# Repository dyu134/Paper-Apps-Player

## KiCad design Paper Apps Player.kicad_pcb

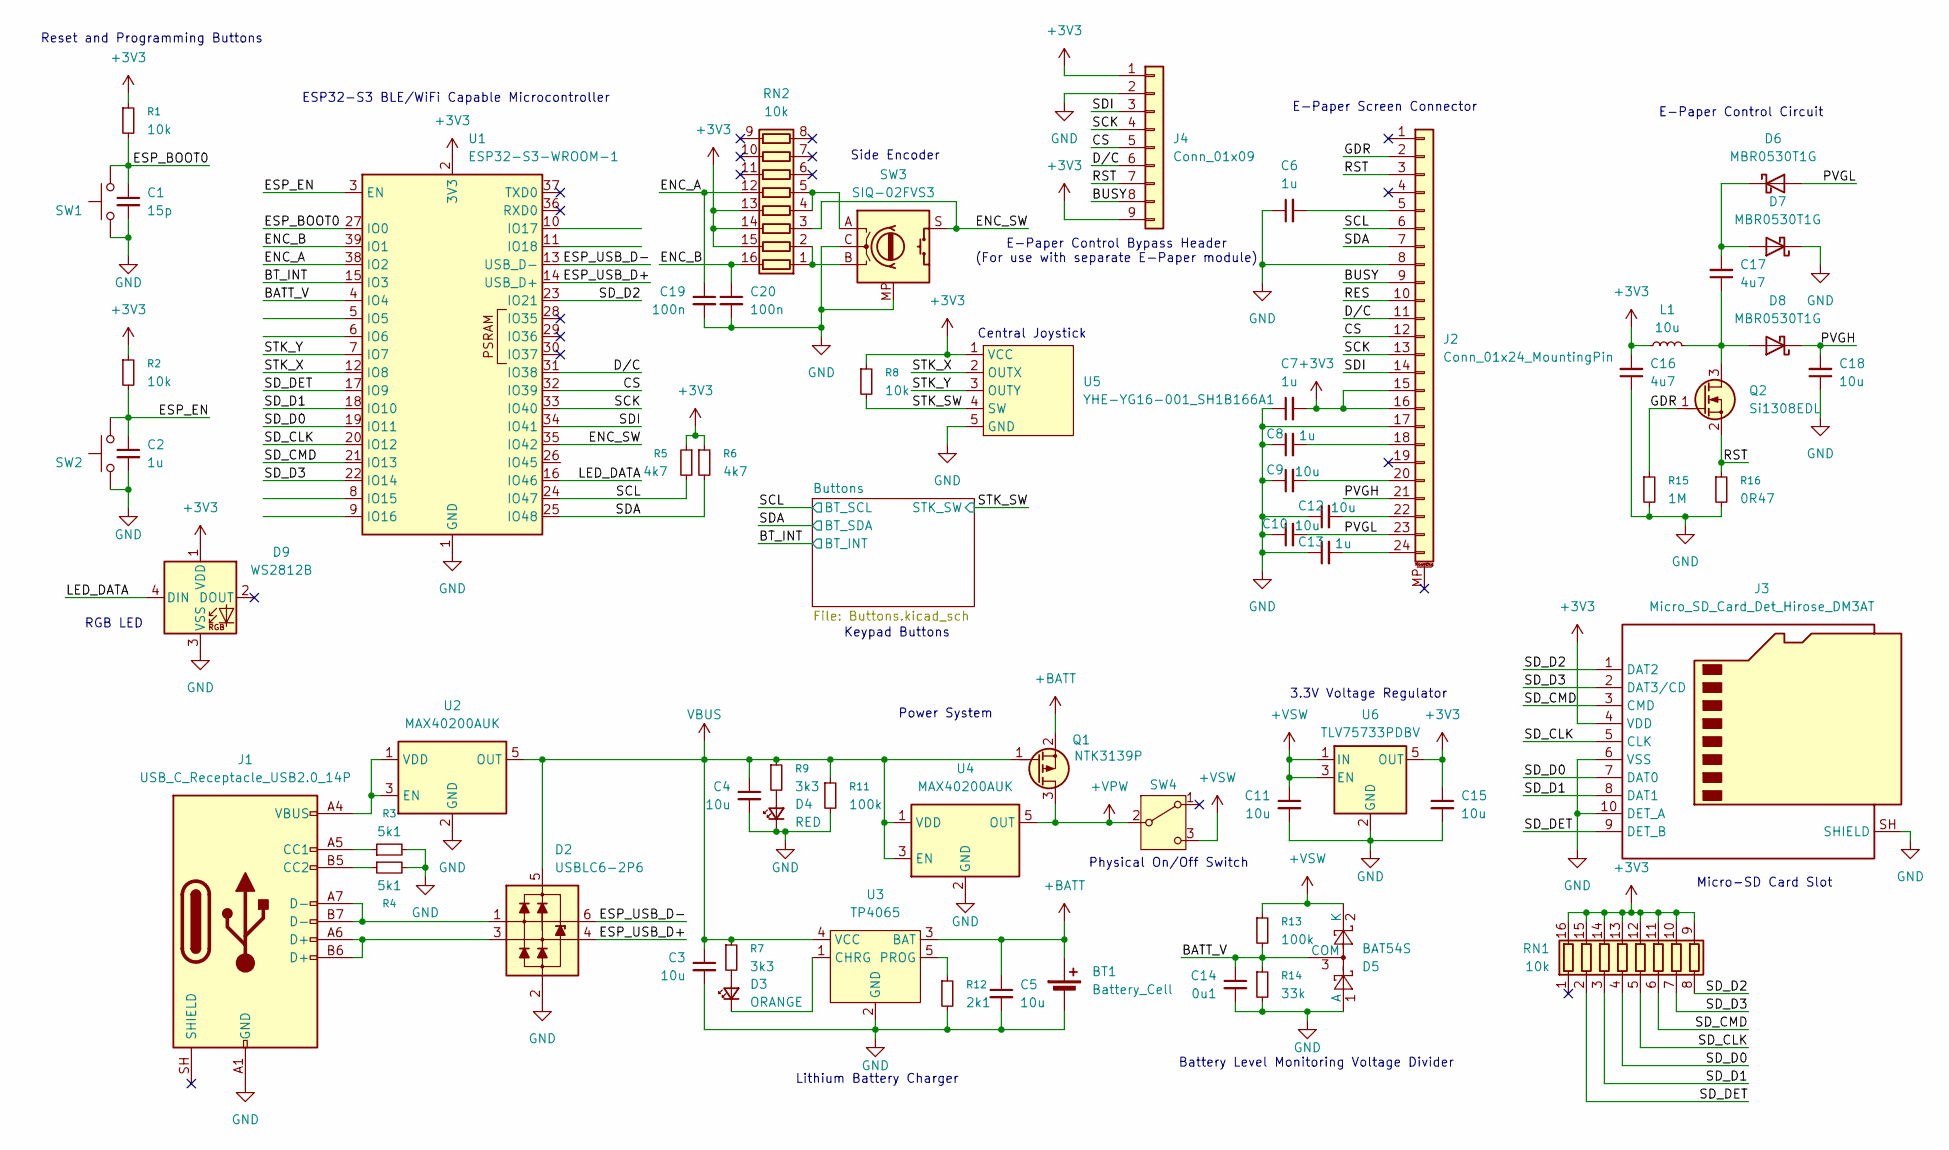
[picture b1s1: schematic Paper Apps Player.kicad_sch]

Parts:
BT1: Battery_Cell; Molex_PicoBlade_53048-0210_1x02_P1.25mm_Horizontal
C1: 15p; C_0603_1608Metric
C2, C6, C7, C8, C13: 1u; C_0603_1608Metric
C3, C4, C5, C9, C10, C11, C12, C15, C18: 10u; C_0603_1608Metric
C14: 0u1; C_0603_1608Metric
C16, C17: 4u7; C_0603_1608Metric
C19, C20: 100n; C_0603_1608Metric
D2: USBLC6-2P6; SOT-666
D3: ORANGE; LED_0603_1608Metric
D4: RED; LED_0603_1608Metric
D5: BAT54S; SOT-23
D6, D7, D8: MBR0530T1G; D_SOD-123
D9: WS2812B; LED_WS2812B_PLCC4_5.0x5.0mm_P3.2mm
J1: USB_C_Receptacle_USB2.0_14P; USB_C_Receptacle_HCTL_HC-TYPE-C-16P-01A
J2: Conn_01x24_MountingPin; Hirose_FH12-24S-0.5SH_1x24-1MP_P0.50mm_Horizontal
J3: Micro_SD_Card_Det_Hirose_DM3AT; microSD_HC_Hirose_DM3AT-SF-PEJM5
J4: Conn_01x09; PinHeader_1x09_P2.54mm_Vertical
L1: 10u; L_0603_1608Metric
Q1: NTK3139P; SOT-723
Q2: Si1308EDL; SOT-323_SC-70
R1, R2: 10k; R_0402_1005Metric
R3, R4: 5k1; R_0603_1608Metric
R5, R6: 4k7; R_0603_1608Metric
R7, R9: 3k3; R_0603_1608Metric
R8: 10k; R_0603_1608Metric
R11, R13: 100k; R_0603_1608Metric
R12: 2k1; R_0603_1608Metric
R14: 33k; R_0603_1608Metric
R15: 1M; R_0603_1608Metric
R16: 0R47; R_0603_1608Metric
RN1, RN2: 10k; R_Array_Convex_8x0602
SW1, SW2: SKRPACE010; SW_Push_1P1T_NO_Vertical_Wuerth_434133025816
SW3: SIQ-02FVS3
SW4: JS102011SAQN; SW_SPDT_CK_JS102011SAQN
U1: ESP32-S3-WROOM-1
U2, U4: MAX40200AUK; SOT-23-5
U3: TP4065; SOT-23-5_HandSoldering
U5: YHE-YG16-001_SH1B166A1
U6: TLV75733PDBV; SOT-23-5

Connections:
+3V3: C7.2, C15.1, C16.2, D9.1 (VDD), J2.15, J2.16, J3.4 (VDD), J4.1, J4.9, L1.1, R1.1, R2.1, R5.1, R6.1, R8.1, RN1.9 (R8.2), RN1.10 (R7.2), RN1.11 (R6.2), RN1.12 (R5.2), RN1.13 (R4.2), RN1.14 (R3.2), RN1.15 (R2.2), RN1.16 (R1.2), RN2.13 (R4.2), RN2.14 (R3.2), RN2.15 (R2.2), U1.2 (3V3), U5.1 (VCC), U6.5 (OUT); also elsewhere on the board
+BATT: BT1.1 (+), C5.1, Q1.2 (S), U3.3 (BAT)
+VPW: Q1.3 (D), SW4.2 (B), U4.5 (OUT)
+VSW: C11.1, D5.2 (K), R13.1, SW4.3 (C), U6.1 (IN), U6.3 (EN)
/BATT_V: C14.1, D5.3 (COM), R13.2, R14.1, U1.4 (IO4)
/BT_INT: U1.15 (IO3); also elsewhere on the board
/BUSY: J2.9, J4.8
/CS: J2.12, J4.5, U1.32 (IO39)
/D/C: J2.11, J4.6, U1.31 (IO38)
/ENC_A: C19.1, RN2.12 (R5.2), U1.38 (IO2)
/ENC_B: C20.1, RN2.16 (R1.2), U1.39 (IO1)
/ENC_SW: RN2.3 (R3.1), SW3.S, U1.35 (IO42)
/ESP_BOOT0: C1.1, R1.2, SW1.2, U1.27 (IO0)
/ESP_EN: C2.1, R2.2, SW2.2, U1.3 (EN)
/ESP_USB_D+: D2.4 (L2), U1.14 (USB_D+)
/ESP_USB_D-: D2.6 (L1), U1.13 (USB_D-)
/GDR: J2.2, Q2.1 (G), R15.1
/LED_DATA: D9.4 (DIN), U1.16 (IO46)
/PVGH: C18.2, D8.1 (K), J2.21
/PVGL: C10.2, D6.2 (A), J2.23
/RES: J2.10
/RST: J2.3, J4.7, Q2.2 (S), R16.1
/SCK: J2.13, J4.4, U1.33 (IO40)
/SCL: J2.6, R5.2, U1.24 (IO47); also elsewhere on the board
/SDA: J2.7, R6.2, U1.25 (IO48); also elsewhere on the board
/SDI: J2.14, J4.3, U1.34 (IO41)
/SD_CLK: J3.5 (CLK), RN1.5 (R5.1), U1.20 (IO12)
/SD_CMD: J3.3 (CMD), RN1.6 (R6.1), U1.21 (IO13)
/SD_D0: J3.7 (DAT0), RN1.4 (R4.1), U1.19 (IO11)
/SD_D1: J3.8 (DAT1), RN1.3 (R3.1), U1.18 (IO10)
/SD_D2: J3.1 (DAT2), RN1.8 (R8.1), U1.23 (IO21)
/SD_D3: J3.2 (DAT3/CD), RN1.7 (R7.1), U1.22 (IO14)
/SD_DET: J3.9 (DET_B), RN1.2 (R2.1), U1.17 (IO9)
/STK_SW: R8.2, U5.4 (SW); also elsewhere on the board
/STK_X: U1.12 (IO8), U5.2 (OUTX)
/STK_Y: U1.7 (IO7), U5.3 (OUTY)
GND: BT1.2 (-), C1.2, C2.2, C3.2, C4.2, C5.2, C6.1, C7.1, C8.1, C9.1, C10.1, C11.2, C12.1, C13.1, C14.2, C15.2, C16.1, C18.1, C19.2, C20.2, D2.2 (VN), D4.1 (K), D5.1 (A), D7.1 (K), D9.3 (VSS), J1.A1 (GND), J1.A12 (GND), J1.B1 (GND), J1.B12 (GND), J2.8, J2.17, J3.6 (VSS), J3.10 (DET_A), J3.SH (SHIELD), J4.2, R3.2, R4.2, R11.2, R12.2, R14.2, R15.2, R16.2, SW1.1, SW2.1, SW3.C, SW3.MP, U1.1 (GND), U1.40 (GND), U1.41 (GND), U2.2 (GND), U3.2 (GND), U4.2 (GND), U5.5 (GND), U6.2 (GND); also elsewhere on the board
unnamed: D2.1 (L1), J1.A7 (D-), J1.B7 (D-)
unnamed: D2.3 (L2), J1.A6 (D+), J1.B6 (D+)
unnamed: D3.2 (A), R7.2
unnamed: D3.1 (K), U3.1 (CHRG)
unnamed: D4.2 (A), R9.2
unnamed: C17.2, D6.1 (K), D7.2 (A)
unnamed: C17.1, D8.2 (A), L1.2, Q2.3 (D)
unnamed: J1.A5 (CC1), R3.1
unnamed: J1.B5 (CC2), R4.1
unnamed: C6.2, J2.5
unnamed: C8.2, J2.18
unnamed: C9.2, J2.20
unnamed: C12.2, J2.22
unnamed: C13.2, J2.24
unnamed: RN2.1 (R1.1), RN2.2 (R2.1), SW3.B
unnamed: RN2.4 (R4.1), RN2.5 (R5.1), SW3.A
unnamed: J1.A4 (VBUS), J1.A9 (VBUS), J1.B4 (VBUS), J1.B9 (VBUS), U2.1 (VDD), U2.3 (EN)
unnamed: R12.1, U3.5 (PROG)
VBUS: C3.1, C4.1, D2.5 (VP), Q1.1 (G), R7.1, R9.1, R11.1, U2.5 (OUT), U3.4 (VCC), U4.1 (VDD), U4.3 (EN)

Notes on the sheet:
Physical On/Off Switch
E-Paper Control Bypass Header (For use with separate E-Paper module)
Power System
Reset and Programming Buttons
Micro-SD Card Slot
Central Joystick
E-Paper Screen Connector
E-Paper Control Circuit
3.3V Voltage Regulator
RGB LED
Keypad Buttons
Lithium Battery Charger
Battery Level Monitoring Voltage Divider
ESP32-S3 BLE/WiFi Capable Microcontroller
Side Encoder

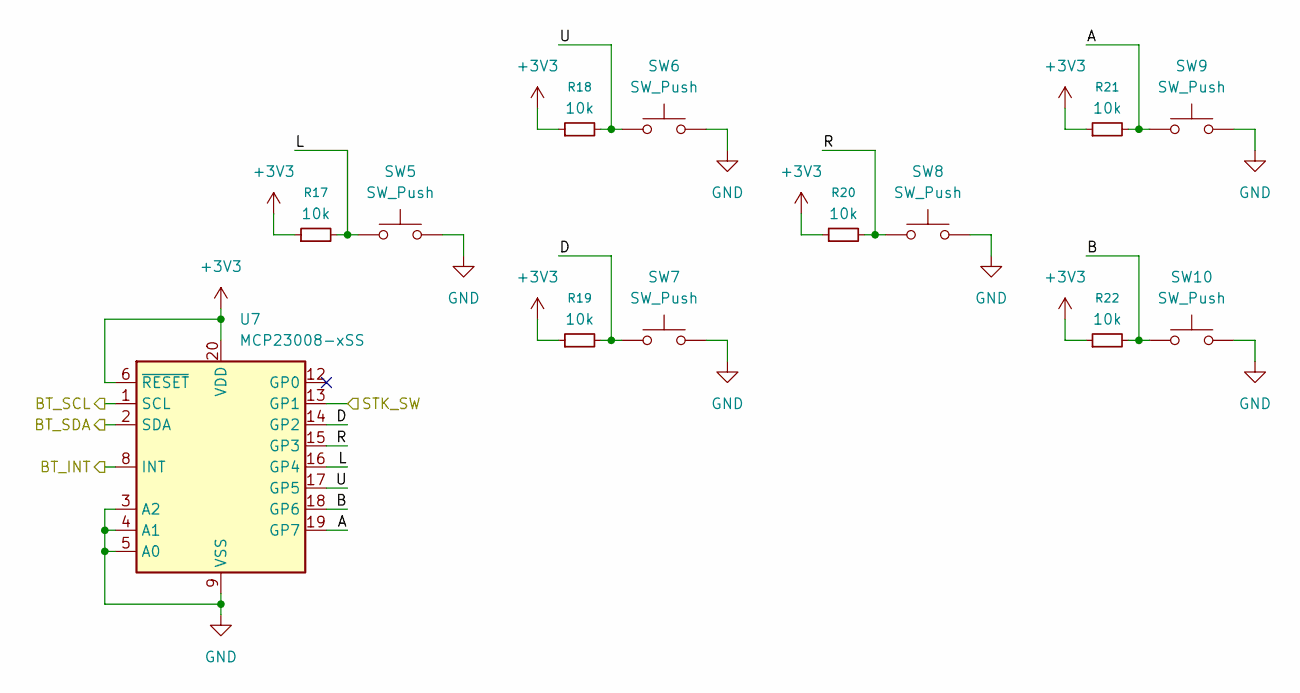
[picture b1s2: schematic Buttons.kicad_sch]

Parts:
R17, R18, R19, R20, R21, R22: 10k; R_0603_1608Metric
SW5, SW6, SW7, SW8, SW9, SW10: SW_Push; SW_SPST_SKQG_WithStem
U7: MCP23008-xSS; SSOP-20_5.3x7.2mm_P0.65mm

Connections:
+3V3: R17.1, R18.1, R19.1, R20.1, R21.1, R22.1, U7.6 (~RESET), U7.20 (VDD); also elsewhere on the board
/BT_INT: U7.8 (INT); also elsewhere on the board
/Buttons/A: R21.2, SW9.1, U7.19 (GP7)
/Buttons/B: R22.2, SW10.1, U7.18 (GP6)
/Buttons/D: R19.2, SW7.1, U7.14 (GP2)
/Buttons/L: R17.2, SW5.1, U7.16 (GP4)
/Buttons/R: R20.2, SW8.1, U7.15 (GP3)
/Buttons/U: R18.2, SW6.1, U7.17 (GP5)
/SCL: U7.1 (SCL); also elsewhere on the board
/SDA: U7.2 (SDA); also elsewhere on the board
/STK_SW: U7.13 (GP1); also elsewhere on the board
GND: SW5.2, SW6.2, SW7.2, SW8.2, SW9.2, SW10.2, U7.3 (A2), U7.4 (A1), U7.5 (A0), U7.9 (VSS); also elsewhere on the board

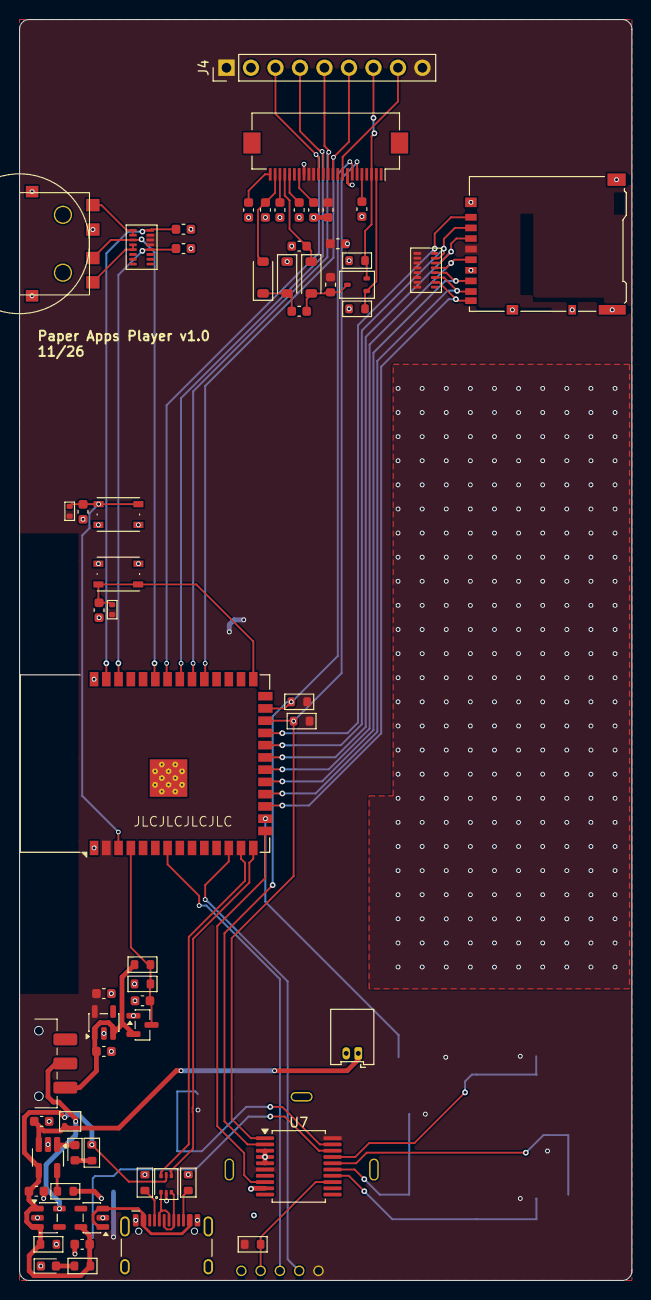
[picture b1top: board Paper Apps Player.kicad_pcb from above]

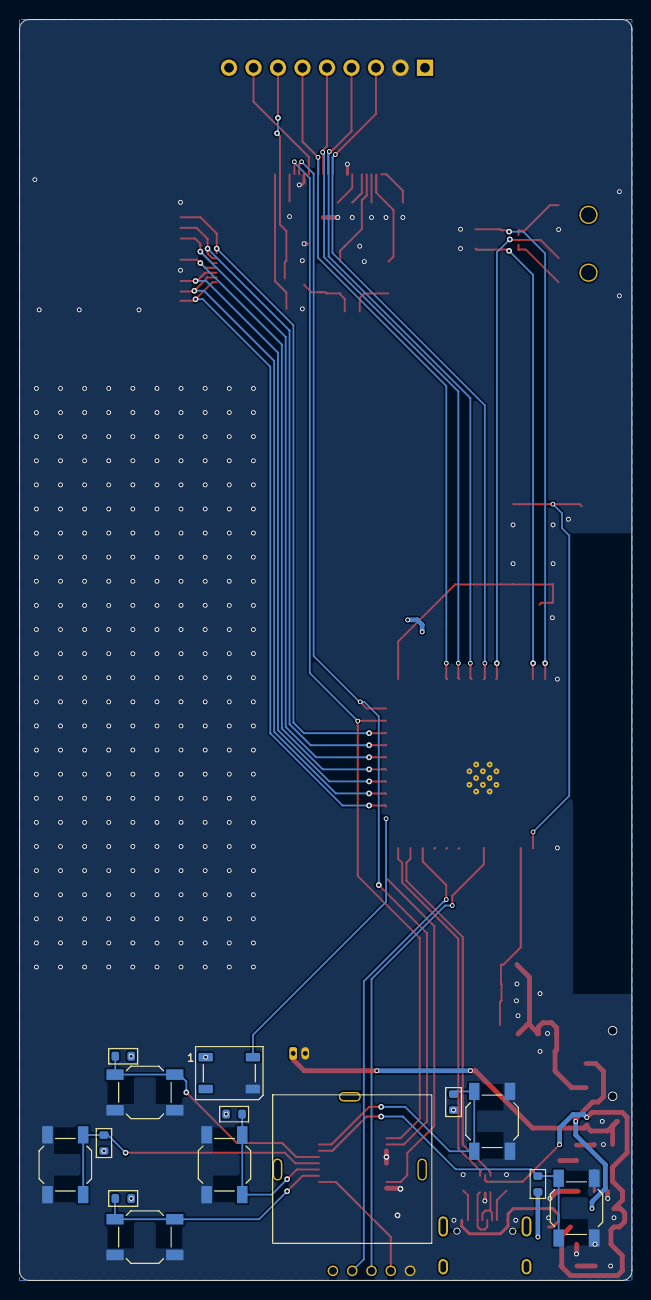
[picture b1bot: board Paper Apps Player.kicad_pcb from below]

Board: 2 copper layers, 63.5 x 130.8 mm, 76 parts (14 on the bottom side), 61 nets.

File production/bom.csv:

Designator,Footprint,Quantity,Value,LCSC Part #
BT1,Molex_PicoBlade_53048-0210_1x02_P1.25mm_Horizontal,1,Battery_Cell,
C1,0603,1,15p,
"C10, C11, C12, C15, C18, C3, C4, C5, C9, L1",0603,10,10u,
"C13, C2, C6, C7, C8",0603,5,1u,
C14,0603,1,0u1,
"C16, C17",0603,2,4u7,
"C19, C20",0603,2,100n,
D2,SOT-666,1,USBLC6-2P6,
D3,0603,1,ORANGE,
D4,0603,1,RED,
D5,SOT-23,1,BAT54S,
"D6, D7, D8",D_SOD-123,3,MBR0530T1G,
D9,LED_WS2812B_PLCC4_5.0x5.0mm_P3.2mm,1,WS2812B,
J1,USB_C_Receptacle_HCTL_HC-TYPE-C-16P-01A,1,USB_C_Receptacle_USB2.0_14P,
J2,Hirose_FH12-24S-0.5SH_1x24-1MP_P0.50mm_Horizontal,1,Conn_01x24_MountingPin,
J3,microSD_HC_Hirose_DM3AT-SF-PEJM5,1,Micro_SD_Card_Det_Hirose_DM3AT,
J4,PinHeader_1x09_P2.54mm_Vertical,1,Conn_01x09,
Q1,SOT-723,1,NTK3139P,
Q2,SOT-323_SC-70,1,Si1308EDL,
"R1, R2",0402,2,10k,
"R11, R13",0603,2,100k,
R12,0603,1,2k1,
R14,0603,1,33k,
R15,0603,1,1M,
R16,0603,1,0R47,
"R17, R18, R19, R20, R21, R22, R8",0603,7,10k,
"R3, R4",0603,2,5k1,
"R5, R6",0603,2,4k7,
"R7, R9",0603,2,3k3,
"RN1, RN2",R_Array_Convex_8x0602,2,10k,
"SW1, SW2",SW_Push_1P1T_NO_Vertical_Wuerth_434133025816,2,SKRPACE010,
"SW10, SW5, SW6, SW7, SW8, SW9",SW_SPST_SKQG_WithStem,6,SW_Push,
SW3,SIQ-02FVS3,1,SIQ-02FVS3,
SW4,SW_SPDT_CK_JS102011SAQN,1,JS102011SAQN,
U1,ESP32-S3-WROOM-1,1,ESP32-S3-WROOM-1,
"U2, U4",SOT-23-5,2,MAX40200AUK,
U3,SOT-23-5_HandSoldering,1,TP4065,
U5,YHE-YG16-001_SH1B166A1,1,YHE-YG16-001_SH1B166A1,
U6,SOT-23-5,1,TLV75733PDBV,
U7,SSOP-20_5.3x7.2mm_P0.65mm,1,MCP23008-xSS,
